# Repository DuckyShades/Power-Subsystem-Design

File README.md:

# Power-Subsystem-Design
This repository contains PCB files for the power subsystem design. Also includes a used datasheet and some external footprints.

## Power Subsystem

The `power` folder contains all the files related to the design and implementation of the power subsystem, responsible for power management and distribution. It includes the following:

- `schematics/`: This directory contains the schematic files for the power circuit, including the main schematic and any supplementary schematics.
- `pcb/`: This directory houses the PCB design files for the power subsystem, including the board layout, Gerber files, and any other relevant PCB design files.
- `firmware/`: This directory contains the firmware code for the microcontroller used in the power subsystem (if applicable), along with any libraries or dependencies required.
- `simulations/`: This directory includes any simulation files or models used for testing and validating the power subsystem's performance.
- `datasheets/`: This directory contains datasheets for the components used in the power subsystem, such as regulators, batteries, and other power management components.
- `docs/`: This directory houses any additional documentation or reports related to the power subsystem, such as design specifications, test reports, or user manuals.

## Importing footprints
- For importing footprints in kicad. the easyeda2kicad script was used.
- `Installation/`: run : "pip install easyeda2kicad" on your terminal
- for more on how to get the lcsc_id and how to import visit website [https://pypi.org/project/easyeda2kicad/]

## Contributing

If you would like to contribute to this project, please follow these steps:

1. Fork the repository
2. Create a new branch for your feature or bugfix
3. Commit your changes to the new branch
4. Push the branch to your forked repository
5. Submit a pull request to the main repository

Please ensure that your contributions adhere to the project's coding standards and guidelines.

## License
This project is not unlicensed.

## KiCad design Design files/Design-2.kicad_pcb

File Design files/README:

## These files were created using kicad 9.0

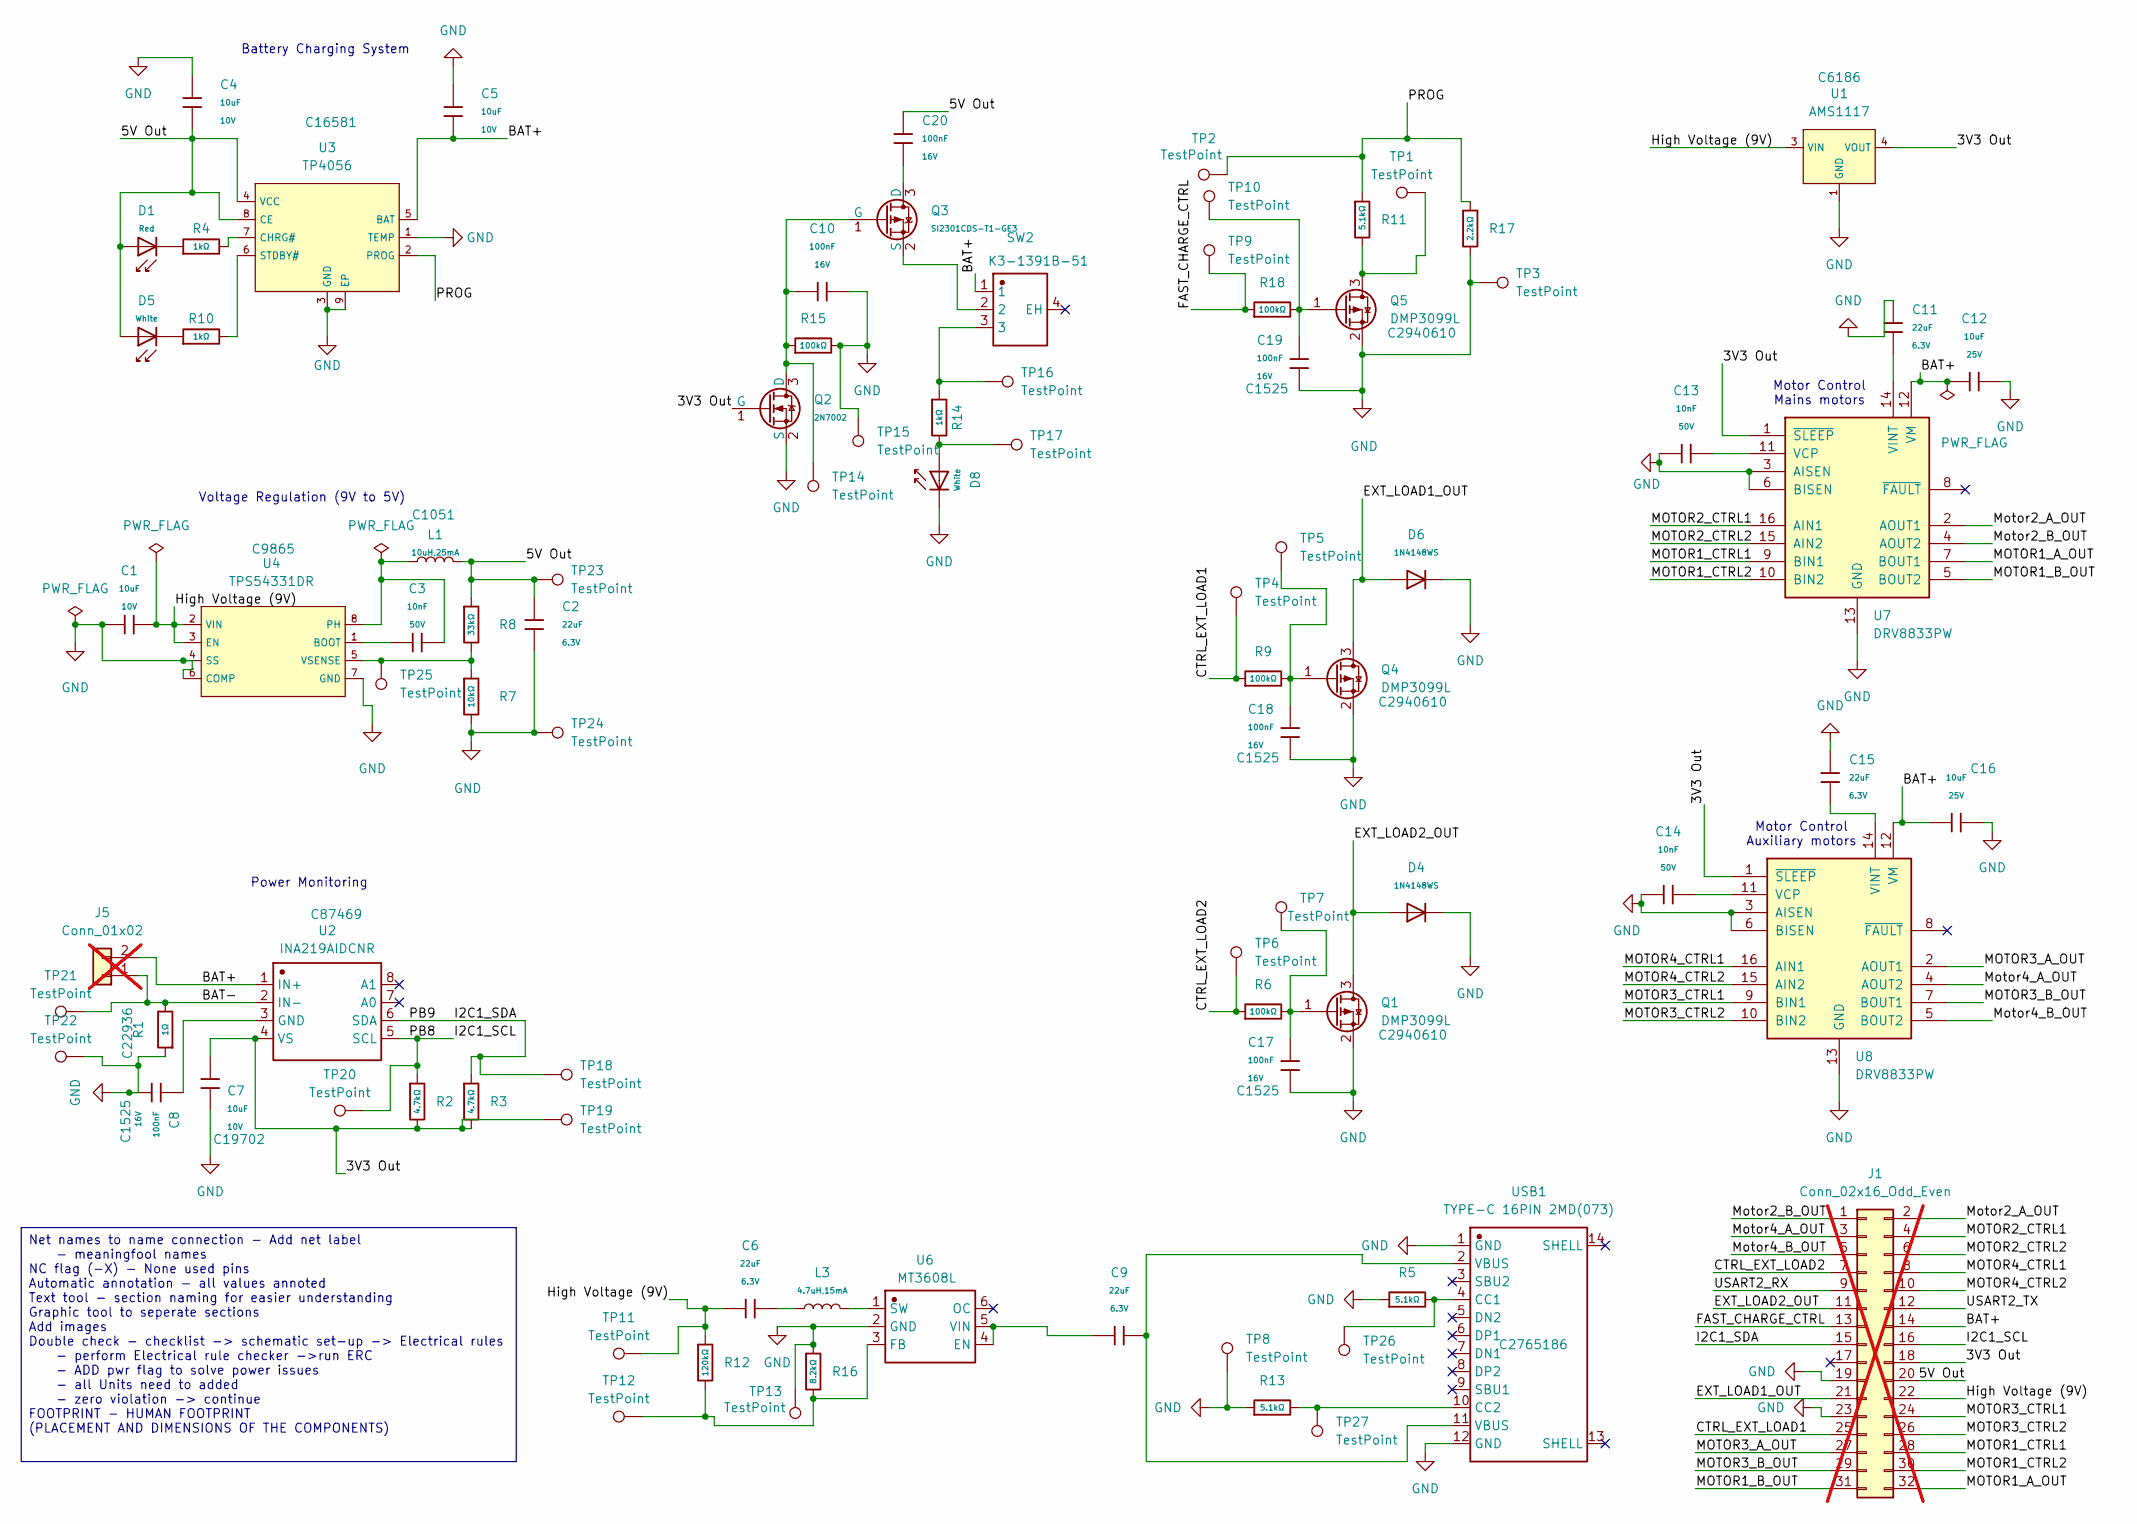
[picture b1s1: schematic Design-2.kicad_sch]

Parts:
C1, C4, C5, C7: 10uF; C_0402_1005Metric_Pad0.74x0.62mm_HandSolder; Voltage Rated 10V; Tolerance ±10%; Part CL10A106KP8NNNC; LCSC C19702
C2, C6, C9, C11, C15: 22uF; C_0402_1005Metric_Pad0.74x0.62mm_HandSolder; Voltage Rated 6.3V; Tolerance ±20%; Part CL10A226MQ8NRNC; LCSC C59461
C3, C13, C14: 10nF; C_0402_1005Metric_Pad0.74x0.62mm_HandSolder; Voltage Rated 50V; Tolerance ±10%; Part CL05B103KB5NNNC; LCSC C15195
C8, C10, C17, C18, C19, C20: 100nF; C_0402_1005Metric_Pad0.74x0.62mm_HandSolder; Voltage Rated 16V; Tolerance ±10%; Part CL05B104KO5NNNC; LCSC C1525
C12, C16: 10uF; C_0402_1005Metric_Pad0.74x0.62mm_HandSolder; Voltage Rated 25V; Tolerance ±10%; Part CL21A106KAYNNNE; LCSC C15850
D1: Red; LED_0805_2012Metric; Part KT-0603R; LCSC C2286
D4, D6: 1N4148WS; D_0402_1005Metric_Pad0.77x0.64mm_HandSolder; Forward Voltage (Vf@If) 1.25V@150mA; Reverse Voltage (Vr) 100V; Part 1N4148WS; LCSC C2128
D5, D8: White; LED_0805_2012Metric; Part KT-0603W; LCSC C2290
J1: Conn_02x16_Odd_Even; PinHeader_2x16_P2.54mm_Vertical; not fitted
J5: Conn_01x02; JST_PH_S2B-PH-K_1x02_P2.00mm_Horizontal; not fitted
L1: 10uH,25mA; L_0402_1005Metric_Pad0.77x0.64mm_HandSolder; Tolerance ±10%; Part CMI321609X100KT; LCSC C1051
L3: 4.7uH,15mA; L_0402_1005Metric_Pad0.77x0.64mm_HandSolder; Tolerance ±10%; Part SDFL1608Q4R7KTF; LCSC C1034
Q1, Q4, Q5: DMP3099L; SOT-23; Part C2940610
Q2: 2N7002; SOT-23; Part 2N7002; LCSC C8545
Q3: SI2301CDS-T1-GE3; SOT-23; Part SI2301CDS-T1-GE3; LCSC C10487
R1: 1Ω; R_0402_1005Metric_Pad0.72x0.64mm_HandSolder; Overload Voltage (Max) 75V; Tolerance ±1%; Part 0603WAF100KT5E; LCSC C22936
R2, R3: 4.7kΩ; R_0402_1005Metric_Pad0.72x0.64mm_HandSolder; Overload Voltage (Max) 50V; Tolerance ±1%; Part 0402WGF4701TCE; LCSC C25900
R4, R10, R14: 1kΩ; R_0402_1005Metric_Pad0.72x0.64mm_HandSolder; Overload Voltage (Max) 50V; Tolerance ±1%; Part 0402WGF1001TCE; LCSC C11702
R5, R11, R13: 5.1kΩ; R_0402_1005Metric_Pad0.72x0.64mm_HandSolder; Overload Voltage (Max) 50V; Tolerance ±1%; Part 0402WGF5101TCE; LCSC C25905
R6, R9, R15, R18: 100kΩ; R_0402_1005Metric_Pad0.72x0.64mm_HandSolder; Overload Voltage (Max) 75V; Tolerance ±1%; Part 0603WAF1003T5E; LCSC C25803
R7: 10kΩ; R_0402_1005Metric_Pad0.72x0.64mm_HandSolder; Overload Voltage (Max) 50V; Tolerance ±1%; Part 0402WGF1002TCE; LCSC C25744
R8: 33kΩ; R_0402_1005Metric_Pad0.72x0.64mm_HandSolder; Overload Voltage (Max) 50V; Tolerance ±1%; Part 0402WGF3302TCE; LCSC C25779
R12: 120kΩ; R_0402_1005Metric_Pad0.72x0.64mm_HandSolder; Overload Voltage (Max) 50V; Tolerance ±1%; Part 0402WGF1203TCE; LCSC C25750
R16: 8.2kΩ; R_0402_1005Metric_Pad0.72x0.64mm_HandSolder; Overload Voltage (Max) 50V; Tolerance ±1%; Part 0402WGF8201TCE; LCSC C25924
R17: 2.2kΩ; R_0402_1005Metric_Pad0.72x0.64mm_HandSolder; Overload Voltage (Max) 50V; Tolerance ±1%; Part 0402WGF2201TCE; LCSC C25879
SW2: K3-1391B-51; SW-TH_K3-1391B-51; Manufacturer Part K3-1391B-51
TP1, TP2, TP3, TP4, TP5, TP6, TP7, TP8, TP9, TP10, TP11, TP12, TP13, TP14, TP15, TP16, TP17, TP18, TP19, TP20, TP21, TP22, TP23, TP24, TP25, TP26, TP27: TestPoint; TestPoint_Pad_D1.0mm
U1: AMS1117; SOT-223-3_TabPin2; Output Voltage 3.3V; Dropout Voltage 1.3V@(800mA); Part AMS1117-3.3; LCSC C6186
U2: INA219AIDCNR; SOIC-16_3.9x9.9mm_P1.27mm; Manufacturer Part INA219AIDCNR
U3: TP4056; SSOP-8_5.25x5.24mm_P1.27mm; Part TP4056-42-ESOP8; LCSC C16581
U4: TPS54331DR; SOIC-8-1EP_3.9x4.9mm_P1.27mm_EP2.29x3mm; Output Voltage 0.8V~25V; Input Voltage 3.5V~28V; Part TPS54331DR; LCSC C9865
U6: MT3608L; SOT-23-6; Manufacturer Part MT3608L
U7, U8: DRV8833PW; TSSOP-16_4.4x5mm_P0.65mm
USB1: TYPE-C 16PIN 2MD(073); USB-C-SMD_TYPE-C-6PIN-2MD-073; Manufacturer Part TYPE-C 16PIN 2MD(073)

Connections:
/3V3 Out: C7.1, J1.18, Q2.1 (G), R2.2, R3.2, TP19.1, U1.2 (VOUT), U1.4 (VOUT), U2.4 (VS), U7.1 (~SLEEP), U8.1 (~SLEEP)
/5V Out: C2.1, C4.2, C20.2, D1.2, D5.2, J1.20, L1.2, R8.1, TP23.1, U3.4 (VCC), U3.8 (CE)
/BAT+: C5.2, C12.1, C16.1, J1.14, J5.2, SW2.1, U2.1 (IN+), U3.5 (BAT), U7.12 (VM), U8.12 (VM)
/BAT-: J5.1, R1.2, TP21.1, U2.2 (IN-)
/CTRL_EXT_LOAD1: J1.25, R9.1, TP4.1
/CTRL_EXT_LOAD2: J1.7, R6.1, TP6.1
/EXT_LOAD1_OUT: D6.2, J1.21, Q4.3 (D)
/EXT_LOAD2_OUT: D4.2, J1.11, Q1.3 (D)
/FAST_CHARGE_CTRL: J1.13, R18.1, TP9.1
/High Voltage (9V): C1.2, C6.1, J1.22, R12.1, TP11.1, U1.3 (VIN), U4.2 (VIN), U4.3 (EN)
/I2C1_SCL: J1.16, R2.1, TP20.1, U2.5 (SCL)
/I2C1_SDA: J1.15, R3.1, TP18.1, U2.6 (SDA)
/MOTOR1_A_OUT: J1.32, U7.7 (BOUT1)
/MOTOR1_B_OUT: J1.31, U7.5 (BOUT2)
/MOTOR1_CTRL1: J1.28, U7.9 (BIN1)
/MOTOR1_CTRL2: J1.30, U7.10 (BIN2)
/MOTOR2_CTRL1: J1.4, U7.16 (AIN1)
/MOTOR2_CTRL2: J1.6, U7.15 (AIN2)
/MOTOR3_A_OUT: J1.27, U8.2 (AOUT1)
/MOTOR3_B_OUT: J1.29, U8.7 (BOUT1)
/MOTOR3_CTRL1: J1.24, U8.9 (BIN1)
/MOTOR3_CTRL2: J1.26, U8.10 (BIN2)
/MOTOR4_CTRL1: J1.8, U8.16 (AIN1)
/MOTOR4_CTRL2: J1.10, U8.15 (AIN2)
/Motor2_A_OUT: J1.2, U7.2 (AOUT1)
/Motor2_B_OUT: J1.1, U7.4 (AOUT2)
/Motor4_A_OUT: J1.3, U8.4 (AOUT2)
/Motor4_B_OUT: J1.5, U8.5 (BOUT2)
/PROG: R11.1, R17.1, TP2.1, U3.2 (PROG)
/USART2_RX: J1.9
/USART2_TX: J1.12
GND: C1.1, C2.2, C4.1, C5.1, C7.2, C8.2, C10.2, C11.1, C12.2, C13.1, C14.1, C15.1, C16.2, C17.2, C18.2, C19.2, D4.1, D6.1, D8.1, J1.19, J1.23, Q1.2 (S), Q2.2 (S), Q4.2 (S), Q5.2 (S), R1.1, R5.1, R7.2, R13.1, R15.2, R16.1, R17.2, TP3.1, TP8.1, TP13.1, TP15.1, TP22.1, TP24.1, U1.1 (GND), U3.1 (TEMP), U3.3 (GND), U3.9 (EP), U4.4 (SS), U4.6 (COMP), U4.7 (GND), U6.2 (GND), U7.3 (AISEN), U7.6 (BISEN), U7.13 (GND), U8.3 (AISEN), U8.6 (BISEN), U8.13 (GND), USB1.1 (GND), USB1.12 (GND)
unnamed: C6.2, L3.1
unnamed: C9.1, USB1.2 (VBUS), USB1.11 (VBUS)
unnamed: D1.1, R4.1
unnamed: D5.1, R10.1
unnamed: D8.2, R14.2, TP17.1
unnamed: C17.1, Q1.1 (G), R6.2, TP7.1
unnamed: C10.1, Q2.3 (D), Q3.1 (G), R15.1, TP14.1
unnamed: C20.1, Q3.3 (D)
unnamed: Q3.2 (S), SW2.2
unnamed: C18.1, Q4.1 (G), R9.2, TP5.1
unnamed: Q5.3 (D), R11.2, TP1.1
unnamed: C19.1, Q5.1 (G), R18.2, TP10.1
unnamed: R14.1, SW2.3, TP16.1
unnamed: C8.1, U2.3 (GND)
unnamed: R4.2, U3.7 (CHRG#)
unnamed: R10.2, U3.6 (STDBY#)
unnamed: C3.1, U4.1 (BOOT)
unnamed: C3.2, L1.1, U4.8 (PH)
unnamed: R7.1, R8.2, TP25.1, U4.5 (VSENSE)
unnamed: C9.2, U6.4 (EN), U6.5 (VIN)
unnamed: R12.2, R16.2, TP12.1, U6.3 (FB)
unnamed: L3.2, U6.1 (SW)
unnamed: C13.2, U7.11 (VCP)
unnamed: C11.2, U7.14 (VINT)
unnamed: C14.2, U8.11 (VCP)
unnamed: C15.2, U8.14 (VINT)
unnamed: R5.2, TP26.1, USB1.4 (CC1)
unnamed: R13.2, TP27.1, USB1.10 (CC2)

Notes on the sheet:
Motor Control Auxiliary motors
Power Monitoring
Motor Control Mains motors
Voltage Regulation (9V to 5V)
Battery Charging System
Net names to name connection - Add net label - meaningfool names NC flag (-X) - None used pins Automatic annotation - all values annoted Text tool - section naming for easier understanding Graphic tool to seperate sections Add images Double check - checklist -> schematic set-up -> Electrical rules 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

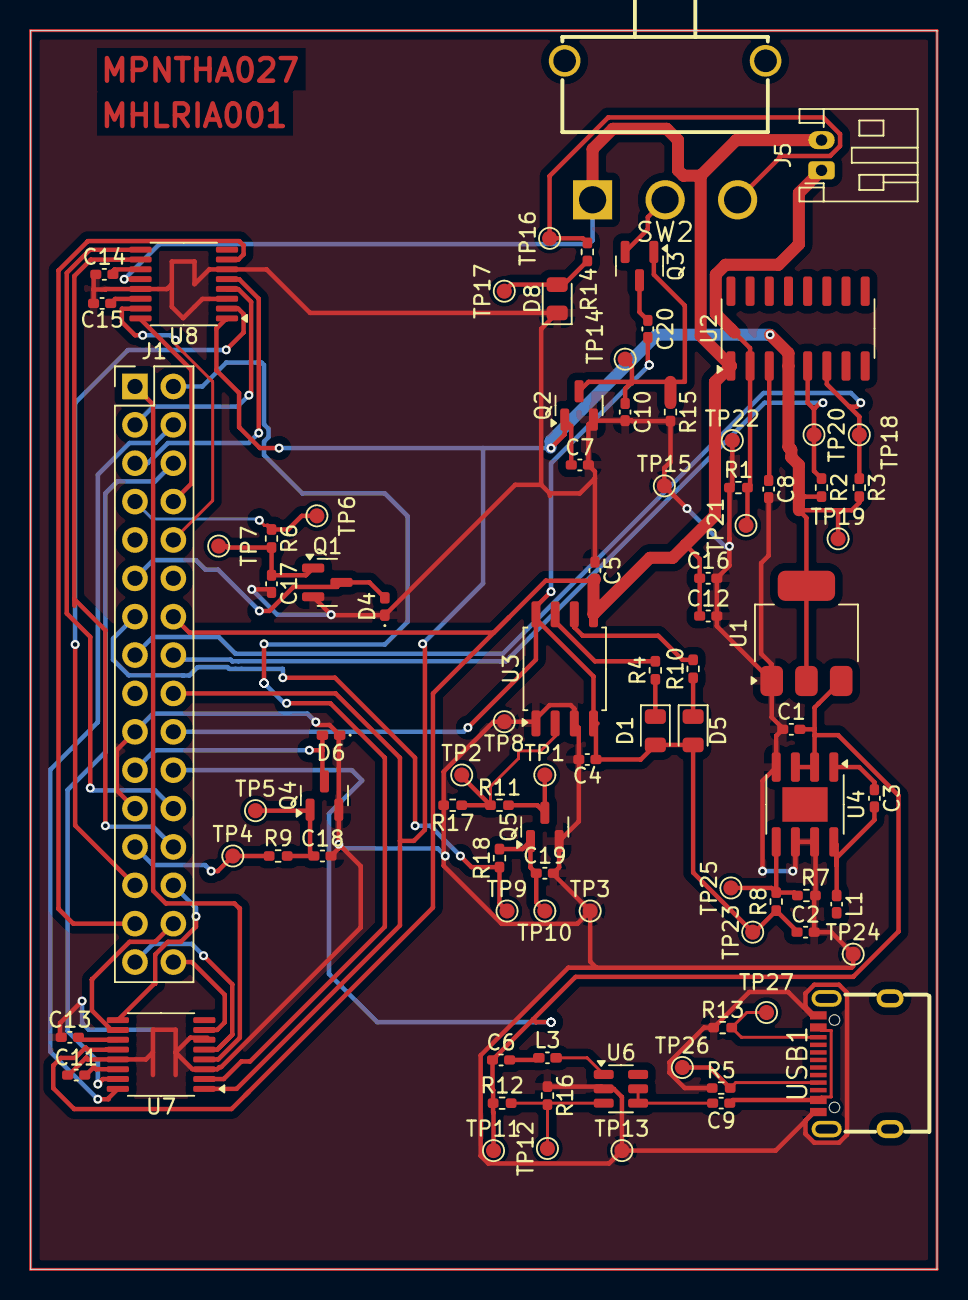
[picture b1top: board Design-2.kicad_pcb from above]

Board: 2 copper layers, 60.0 x 82.0 mm, 88 parts (0 on the bottom side), 58 nets.

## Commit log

2025-04-21 Datasheets README
2025-04-21 Import Footprints and Schematics
